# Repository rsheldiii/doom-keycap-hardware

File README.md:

# Doom Keycap Hardware Repository

Here are all the files associated with the hardware for the Doom Keycap. If you're looking for the code, it's [here](https://github.com/rsheldiii/rp2040-doom-LCD/).

I had every intention of fabricating and selling these myself, but I got caught up on how to manufacture the keycap itself without A. breaking the bank, or B. doing a group buy before realizing my design wasn't feasible. With that, coupled with (happy) life events, I decided to open-source the hardware now.

## Doom Business Card

I handed out quite a few of these during OpenSauce 2025! You can check the subfolder for the front paste file (which you can use to generate a highly-recommended stencil at osh stencils) and the BOM. Happy soldering and good luck!

## Doom Keycap Kicad

This directory houses the Kicad files for the final version of the Doom Keycap PCB. It was essentially a mashup of the RP2040 minimal pcb and Adafruit's schematic for the [MAX98357AETE breakout board](https://learn.adafruit.com/adafruit-max98357-i2s-class-d-mono-amp/downloads), with a semi-standard FPC connector for SPI displays and smaller parts. Quick facts:

* The footprint library did not make the jump to a new operating system, but the footprints are embedded in the PCB file; you can right-click "edit footprint", save-as, and then reassociate them in the schematic. Or you know, you could not.
* I used screens from [this](https://www.aliexpress.us/item/3256803794221438.html?spm=a2g0o.order_list.order_list_main.4.651c1802EaKSD2&gatewayAdapt=glo2usa) aliexpress listing, which have FPC connectors that look like [this](https://imgur.com/btXJBdo). No other FPC connector will work on this iteration of the board (obviously)
* Finding a small but powerful enough speaker was a challenge. The small screen versions of the keycap did not have a speaker installed due to size constraints.
* I calculated the value of the crystal oscillator's capacitors wrong; it starts up, but it requires an extra flag during program compilation to give the crystal more time to stabilize. It should work as-is, but optimizing those values would be ideal
* The hardware design / components selected might not be well-optimized, I'm a computer scientist by trade. I did my best though.
* The flash memory could definitely be smaller, but beware: not all memory chips are drop-in replacements. Similarly, the voltage regulator could have a much smaller footprint, I just couldn't find one at the time. If you do swap the regulator and you want to play doom on the keycap with a keyboard, remember the regulator will be supplying electricity to the keyboard, not the other way around. 

## Doom Keycap Case

Here are the final couple STLs I generated for the model, plus the fusion 360 file I used to generate them. 

* the f3d file should have comments in the parameters section about the size of the larger screen, if you wish to make the large version of the keycap.
* If you want to install a speaker on the small version, you'll need to increase the space available to the PCB
* These parts were printed on a resin printer in transparent resin, processed, and then hit with clear gloss lacquer. My plan was to switch to an acrylic insert for mass production.

## Fabrication tips

* Unless you are a god-tier solderer, you're not going to get away with hand-soldering these boards; you will need a stencil and a reflow oven or similar. OSHPark has a sister-service for cheap stencils, which is what I used.
* You _can_ get away with a single stencil for the top of the board and hand-soldering the bottom though. the only tricky part is the FPC connector, but with extra flux and dragging the tip, the solder should wick where it needs to go. 
* The LED on the board is keyed to blink at certain critical moments in the program; if you aren't getting _any_ blinking at all, it means the device is malfunctioning. If you get _some_ blinking that stops, you probably forgot to burn the wad file to memory - I can't tell you how many times I did this. A screen does not have to be installed for the program to run successfully.
* if you upload a program that runs fine, but is then forgotten, you need to set PICO_XOSC_STARTUP_DELAY_MULTIPLIER. The crystal isn't stabilizing fast enough, which is causing the RP2040 to give up on reading the flash chip
* Fitment on the case is very tight; try not to over-bend the FPC on the screen
* Power can be delivered through the USB connector, or through the pads on the bottom of the PCB (refer to schematic for polarity). The voltage regulator in the BOM has more than enough power to run a simple keyboard, though I would be careful with LED keyboards. 1S lipos should work as well. If you want to use another power source, there are very many voltage regulators in the SOT223 package

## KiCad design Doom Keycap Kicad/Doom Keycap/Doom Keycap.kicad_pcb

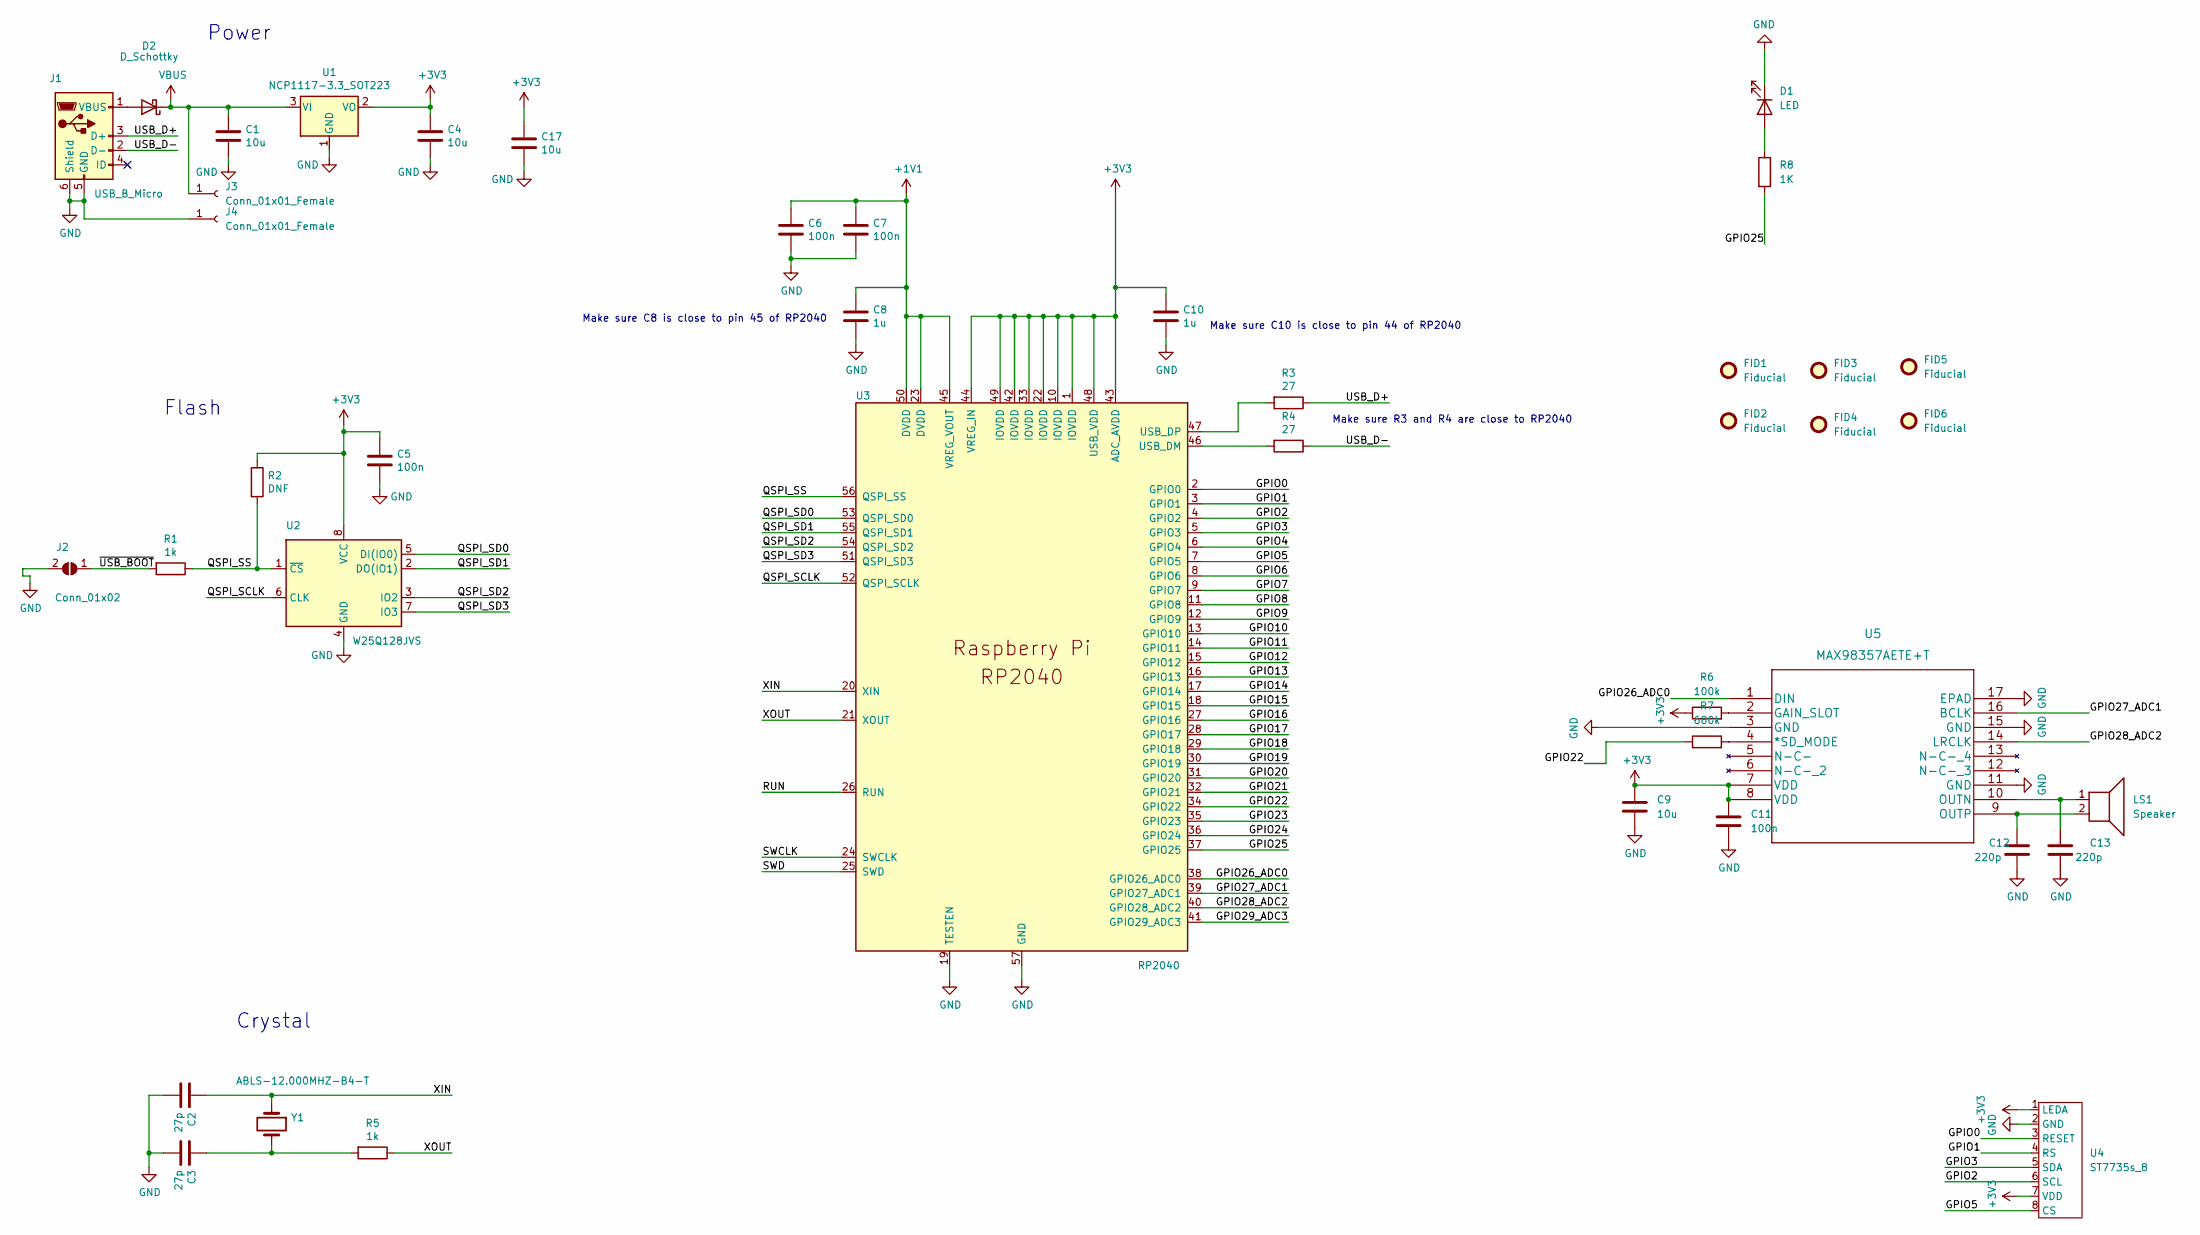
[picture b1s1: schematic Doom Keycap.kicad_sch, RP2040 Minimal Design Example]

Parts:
C1, C4, C9, C17: 10u; C_0402_1005Metric
C2, C3: 27p; C_0402_1005Metric
C5, C6, C7, C11: 100n; C_0402_1005Metric
C8, C10: 1u; C_0402_1005Metric
C12, C13: 220p; C_0402_1005Metric
D1: LED; LED_0603_1608Metric
D2: D_Schottky; D_0402_1005Metric
FID1, FID2, FID3, FID4, FID5, FID6: Fiducial; Fiducial_0.5mm_Mask1mm
J1: USB_B_Micro; USB_Micro-B_Amphenol_10103594-0001LF_Horizontal_modified
J2: Conn_01x02; SolderJumper-2_P1.3mm_Open_Pad1.0x1.5mm
J3, J4: Conn_01x01_Female; TestPoint_Pad_D1.0mm
LS1: Speaker; SMS-1308MS-2-R
R1, R5: 1k; R_0402_1005Metric
R2: DNF; R_0402_1005Metric
R3, R4: 27; R_0402_1005Metric
R6: 100k; R_0402_1005Metric
R7: 680k; R_0402_1005Metric
R8: 1K; R_0402_1005Metric
U1: NCP1117-3.3_SOT223; SOT-223-3_TabPin2
U2: W25Q128JVS; SOIC-8_5.23x5.23mm_P1.27mm
U3: RP2040; RP2040-QFN-56
U4: ST7735s_8; 2328702-8
U5: MAX98357AETE+T; MAX98357AETE-T
Y1: ABLS-12.000MHZ-B4-T; 403C35D12M00000

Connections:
+1V1: C6.1, C7.1, C8.1, U3.23 (DVDD), U3.45 (VREG_VOUT), U3.50 (DVDD)
+3V3: C4.1, C5.1, C9.1, C10.1, C11.1, C17.1, R2.1, R6.1, U1.2 (VO), U2.8 (VCC), U3.1 (IOVDD), U3.10 (IOVDD), U3.22 (IOVDD), U3.33 (IOVDD), U3.42 (IOVDD), U3.43 (ADC_AVDD), U3.44 (VREG_IN), U3.48 (USB_VDD), U3.49 (IOVDD), U4.1 (LEDA), U4.7 (VDD), U5.7 (VDD), U5.8 (VDD)
/GPIO0: U3.2 (GPIO0), U4.3 (RESET)
/GPIO1: U3.3 (GPIO1), U4.4 (RS)
/GPIO2: U3.4 (GPIO2), U4.6 (SCL)
/GPIO3: U3.5 (GPIO3), U4.5 (SDA)
/GPIO4: U3.6 (GPIO4)
/GPIO5: U3.7 (GPIO5), U4.8 (CS)
/GPIO6: U3.8 (GPIO6)
/GPIO7: U3.9 (GPIO7)
/GPIO8: U3.11 (GPIO8)
/GPIO9: U3.12 (GPIO9)
/GPIO10: U3.13 (GPIO10)
/GPIO11: U3.14 (GPIO11)
/GPIO12: U3.15 (GPIO12)
/GPIO13: U3.16 (GPIO13)
/GPIO14: U3.17 (GPIO14)
/GPIO15: U3.18 (GPIO15)
/GPIO16: U3.27 (GPIO16)
/GPIO17: U3.28 (GPIO17)
/GPIO18: U3.29 (GPIO18)
/GPIO19: U3.30 (GPIO19)
/GPIO20: U3.31 (GPIO20)
/GPIO21: U3.32 (GPIO21)
/GPIO22: R7.1, U3.34 (GPIO22)
/GPIO23: U3.35 (GPIO23)
/GPIO24: U3.36 (GPIO24)
/GPIO25: R8.2, U3.37 (GPIO25)
/GPIO26_ADC0: U3.38 (GPIO26_ADC0), U5.1 (DIN)
/GPIO27_ADC1: U3.39 (GPIO27_ADC1), U5.16 (BCLK)
/GPIO28_ADC2: U3.40 (GPIO28_ADC2), U5.14 (LRCLK)
/GPIO29_ADC3: U3.41 (GPIO29_ADC3)
/QSPI_SCLK: U2.6 (CLK), U3.52 (QSPI_SCLK)
/QSPI_SD0: U2.5 (DI(IO0)), U3.53 (QSPI_SD0)
/QSPI_SD1: U2.2 (DO(IO1)), U3.55 (QSPI_SD1)
/QSPI_SD2: U2.3 (IO2), U3.54 (QSPI_SD2)
/QSPI_SD3: U2.7 (IO3), U3.51 (QSPI_SD3)
/QSPI_SS: R1.1, R2.2, U2.1 (~CS), U3.56 (QSPI_SS)
/RUN: U3.26 (RUN)
/SWCLK: U3.24 (SWCLK)
/SWD: U3.25 (SWD)
/USB_D+: J1.3 (D+), R3.1
/USB_D-: J1.2 (D-), R4.1
/XIN: C2.1, U3.20 (XIN), Y1.1
/XOUT: R5.1, U3.21 (XOUT)
/~USB_BOOT: J2.1 (A), R1.2
GND: C1.2, C2.2, C3.2, C4.2, C5.2, C6.2, C7.2, C8.2, C9.2, C10.2, C11.2, C12.2, C13.2, C17.2, D1.1 (K), J1.5 (GND), J1.6 (Shield), J2.2 (B), J4.1, U1.1 (GND), U2.4 (GND), U3.19 (TESTEN), U3.57 (GND), U4.2 (GND), U5.3 (GND), U5.11 (GND), U5.15 (GND), U5.17 (EPAD)
unnamed: C3.1, R5.2, Y1.2
unnamed: C12.1, LS1.2, U5.9 (OUTP)
unnamed: C13.1, LS1.1, U5.10 (OUTN)
unnamed: D1.2 (A), R8.1
unnamed: D2.2 (A), J1.1 (VBUS)
unnamed: R3.2, U3.47 (USB_DP)
unnamed: R4.2, U3.46 (USB_DM)
unnamed: R6.2, U5.2 (GAIN_SLOT)
unnamed: R7.2, U5.4 (*SD_MODE)
VBUS: C1.1, D2.1 (K), J3.1, U1.3 (VI)

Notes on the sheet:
Make sure C8 is close to pin 45 of RP2040
Make sure C10 is close to pin 44 of RP2040
Make sure R3 and R4 are close to RP2040
Flash
Crystal
Power

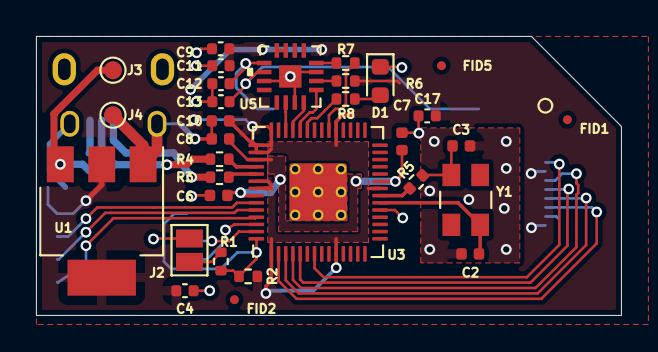
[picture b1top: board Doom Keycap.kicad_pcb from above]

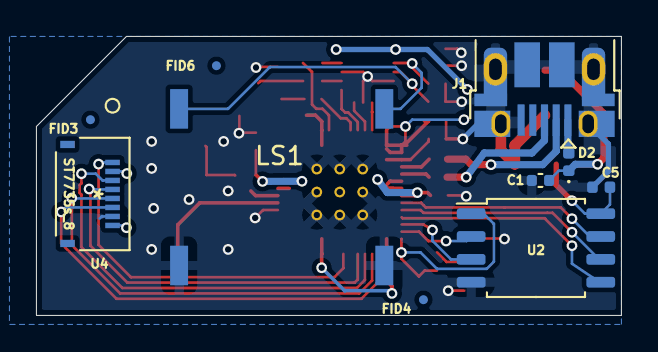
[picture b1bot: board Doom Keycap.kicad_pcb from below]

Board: 2 copper layers, 32.5 x 15.5 mm, 41 parts (10 on the bottom side), 34 nets.

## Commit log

2024-04-24 Fix gerbers
2025-07-26 add doom business card F_Paste layer
2025-07-26 add BOM for business card and restructure

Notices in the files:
parts and their libraries:
Copyright 2021 Accelerated Designs. All rights reserved.
